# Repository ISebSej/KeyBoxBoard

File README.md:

# RICHARD (Robust Internal Controller for the High Altitude Rocket Dolken)

Clone this repository using

    git clone --recursive https://github.com/DanSTAR-DTU/RICHARD-MKII

## >>> Submodule <<<

IMPORTANT: After cloning this repository WITHOUT using `--recursive`, run

    git submodule update --init
    
so that the 'danstar-kicad-lib' is downloaded from its separate repository.

### Pulling upstream changes

If the submodule has been updated and you require these changes, run

    git submodule update --remote
    
to get the latest changes from the submodule repository.
Remember to push the changes as you do all other changes.

### Pushing local changes

Changes made to the submodule locally needs to be uploaded to the remote repository,
this is done by entering the submodule folder using

    cd danstar-kicad-lib
    
Checkout the master branch (this step is EXTREMELY important and recommended by doctors around the globe)

    git checkout master
    
Then adding any changes made (please ensure the changes are valid and non-breaking, unless coordinated with the electro group)

    git add -A
    
Commit the changes with a message describing the changes

    git commit -m "I HAVE NO CLUE WHAT I DID"

Finally, push the changes using

    git push

### Further reading

https://git-scm.com/book/en/v2/Git-Tools-Submodules

### What to do if something breaks and/or git goes all "heey woah there, sonny jim"

DON'T PANIC! In most cases the situation can be fixed.
Use Google (and your brain) and see if you can't get yourself out of whatever situation you put yourself in
-OR-
if you don't feel comfortable messing with git, ask Sebastian Tibor on Slack or Facebook

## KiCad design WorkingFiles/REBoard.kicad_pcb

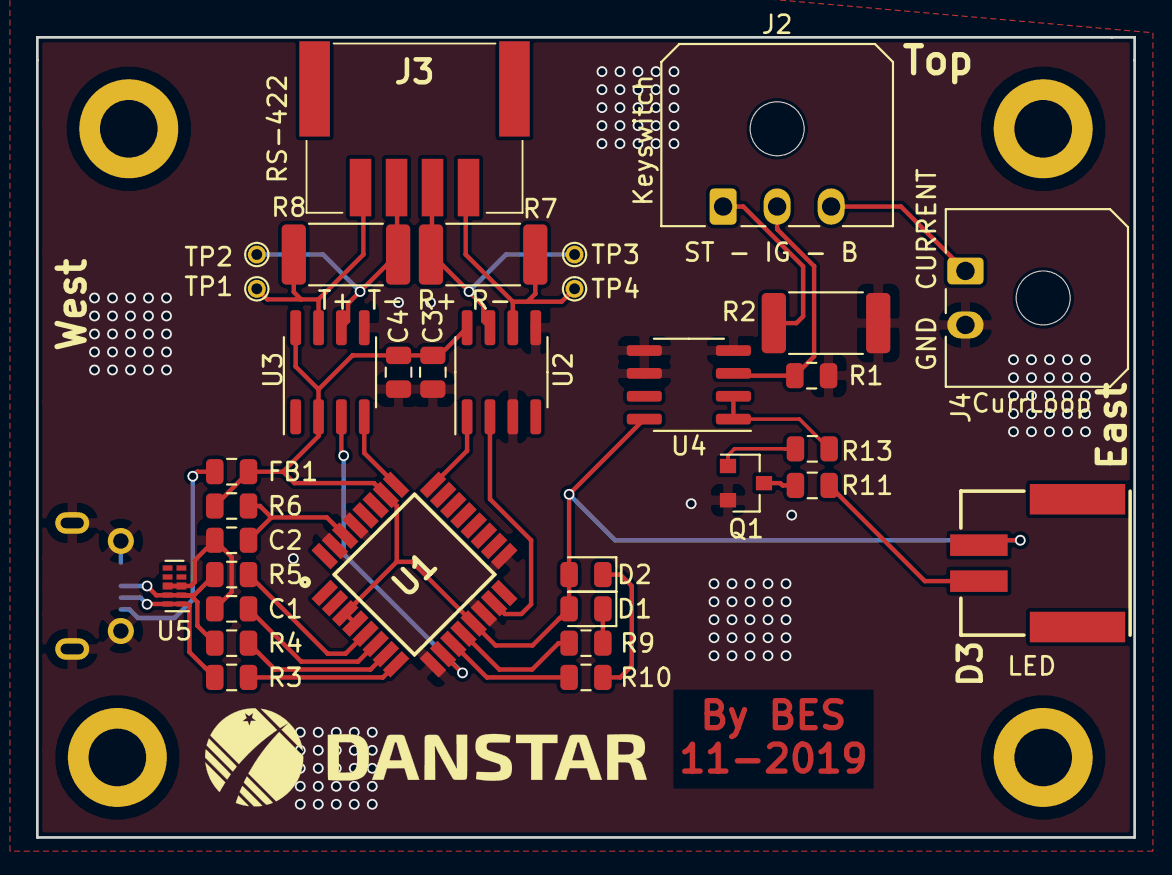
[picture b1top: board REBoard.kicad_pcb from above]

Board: 2 copper layers, 61.0 x 44.5 mm, 34 parts (1 on the bottom side), 29 nets.

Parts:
C1: 33n; C_0805_2012Metric
C2: 0u1; C_0805_2012Metric
C3, C4: C; C_0805_2012Metric
D1, D2: LED; D_0805_2012Metric
D3: LED; Molex2pin_502352_0200-DanSTAR_Duraclick
FB1: Ferrite_Bead; L_0805_2012Metric
J1: USB_B_-_DanSTAR_USB; USB_Micro-1050170001-DanSTAR_USB
J2: Conn_01x03_-_DanSTAR_Generic_Connector; Molex_Micro-Fit_3.0_43650-0300_1x03_P3.00mm_Horizontal
J3: Conn_01x04_-_DanSTAR_Generic_Connecoter; Molex4pin_502352_0400-DanSTAR_Duraclick
J4: Conn_01x02_-_DanSTAR_Generic_Connector; Molex_Micro-Fit_3.0_43650-0200_1x02_P3.00mm_Horizontal
Q1: BC817; SOT-23-DanSTAR_USB_Disc
R1: 10k; R_0805_2012Metric
R2: 70; R_2512_6332Metric
R3, R4: 27; R_0805_2012Metric
R5: 1k5; R_0805_2012Metric
R6: 470; R_0805_2012Metric
R7, R8: 120; R_2512_6332Metric
R9, R10, R11: 220; R_0805_2012Metric
R13: 20k; R_0805_2012Metric
TP1, TP2, TP3, TP4: TestPoint_-_DanSTAR_Test; TestPoint-DanSTAR_TestPoint
U1: FT232BL; QFP80P900X900X120-32N
U2, U3: MAX481EESA; SOIC-8-DanSTAR_InstrAmpl
U4: LM358; SOIC-8-DanSTAR_InstrAmpl
U5: TPD4E02B04; USON-10-DanSTAR_ESD_Prot

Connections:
+5V: C3.2, C4.2, D1.2, D2.2, D3.2, FB1.1, R6.1, U1.3, U1.4, U1.13, U1.26, U2.8, U3.2, U3.8, U4.8
/ARM_LED_SIG: R13.2, U4.1, U4.2
/B: J2.3, J4.1
/D+: J1.3, R4.2, R5.2, U5.2, U5.9
/D-: J1.2, R3.2, U5.1, U5.10
/IG: J2.2, R1.1, U4.3
/PWREN: U1.15, U2.2
/RXD: U1.24, U2.1
/RXLED: R10.2, U1.11
/Rx+: J3.3, R7.1, TP3.1, U2.7
/Rx-: J3.4, R7.2, TP4.1, U2.6
/SLEEP: U1.10, U3.3
/ST: J2.1, R2.1
/TXD: U1.25, U3.4
/TXLED: R9.2, U1.12
/Tx+: J3.1, R8.1, TP1.1, U3.7
/Tx-: J3.2, R8.2, TP2.1, U3.6
/VBUS: FB1.2, J1.1
GND: C1.2, C2.2, C3.1, C4.1, J1.5, J1.6, J4.2, Q1.2, R1.2, R2.2, U1.9, U1.14, U1.17, U1.29, U1.31, U2.3, U2.5, U3.5, U4.4, U4.5, U4.6, U5.3, U5.8
unnamed: C1.1, U1.6
unnamed: C2.1, R6.2, U1.30
unnamed: D1.1, R9.1
unnamed: D2.1, R10.1
unnamed: D3.1, R11.1
unnamed: Q1.1, R13.1
unnamed: Q1.3, R11.2
unnamed: R3.1, U1.8
unnamed: R4.1, U1.7
unnamed: R5.1, U1.5

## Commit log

2020-11-11 BES - Initial commit
2020-11-11 BES - include .gitignore
2020-11-11 BES - remove readme
2021-06-10 Rearrage Folders
2021-06-10 Minor Change
